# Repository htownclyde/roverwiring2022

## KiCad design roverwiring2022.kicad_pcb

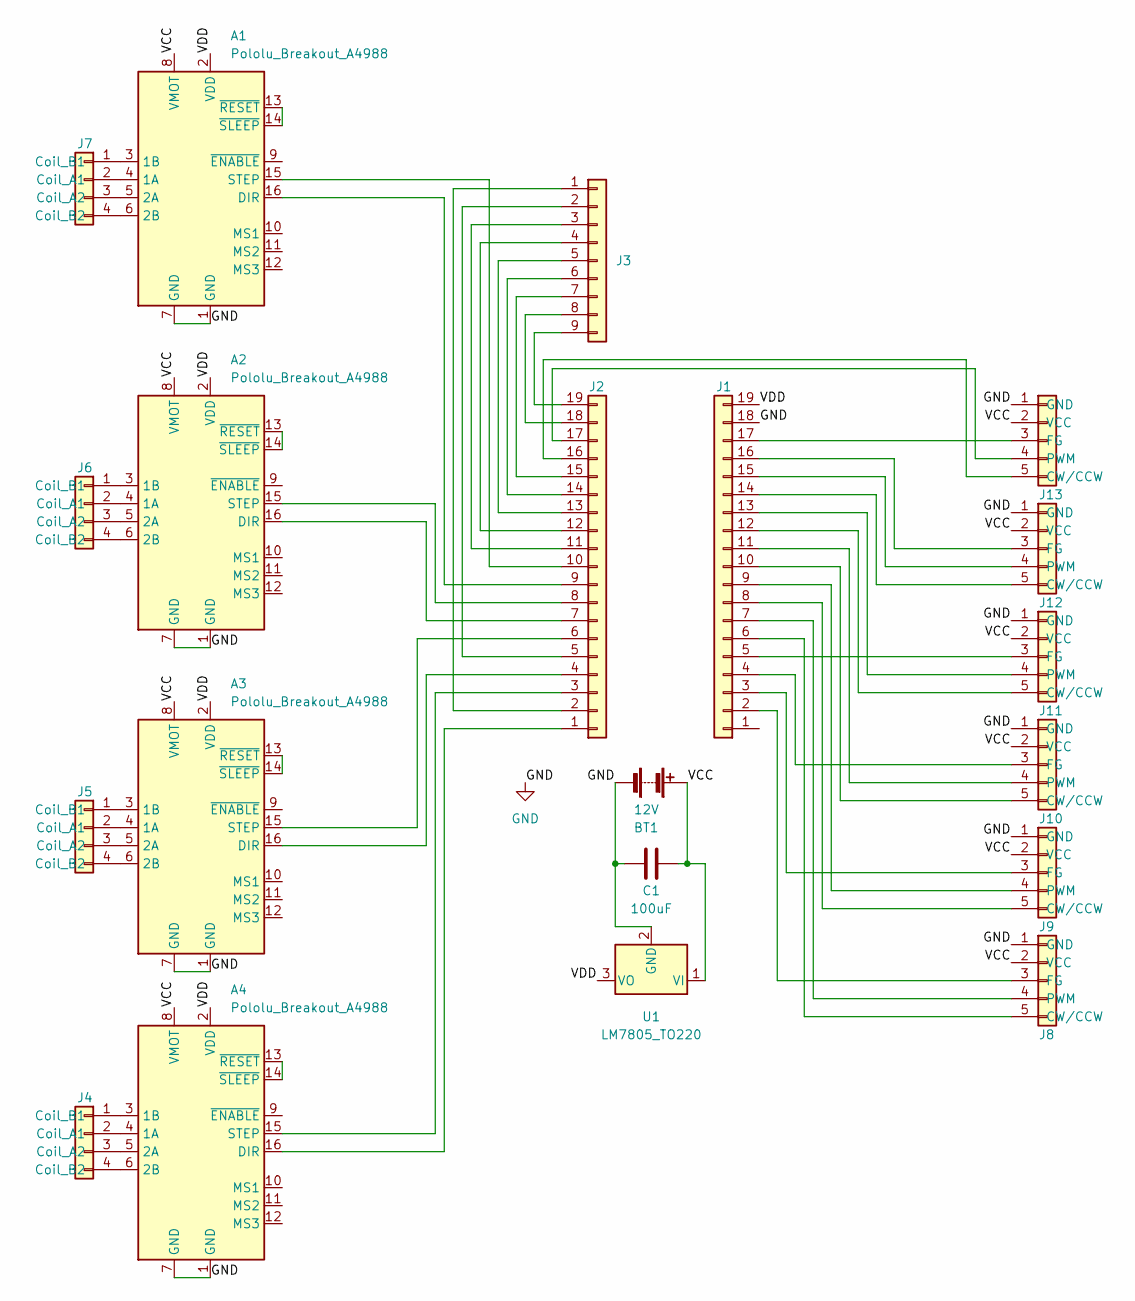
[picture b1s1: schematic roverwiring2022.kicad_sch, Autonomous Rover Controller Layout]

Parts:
A1, A2, A3, A4: Pololu_Breakout_A4988; Pololu_Breakout-16_15.2x20.3mm
BT1: 12V; BarrelJack_CLIFF_FC681465S_SMT_Horizontal
C1: 100uF; CP_Axial_L10.0mm_D4.5mm_P15.00mm_Horizontal
J1, J2: Conn_01x19; PinHeader_1x19_P2.54mm_Vertical
J3: Conn_01x09; PinHeader_1x09_P2.54mm_Vertical
J4, J5, J6, J7: Conn_01x04; PinHeader_1x04_P2.54mm_Vertical
J8, J9, J10, J11, J12, J13: Conn_01x05; PinHeader_1x05_P2.54mm_Vertical
U1: LM7805_TO220; TO-220-3_Vertical

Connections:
/VCC: A1.8 (VMOT), A2.8 (VMOT), A3.8 (VMOT), A4.8 (VMOT), BT1.1 (+), C1.2, J8.2 (VCC), J9.2 (VCC), J10.2 (VCC), J11.2 (VCC), J12.2 (VCC), J13.2 (VCC), U1.1 (VI)
/VDD: A1.2 (VDD), A2.2 (VDD), A3.2 (VDD), A4.2 (VDD), J1.19, U1.3 (VO)
GND: A1.1 (GND), A1.7 (GND), A2.1 (GND), A2.7 (GND), A3.1 (GND), A3.7 (GND), A4.1 (GND), A4.7 (GND), BT1.2 (-), C1.1, J1.18, J8.1 (GND), J9.1 (GND), J10.1 (GND), J11.1 (GND), J12.1 (GND), J13.1 (GND), U1.2 (GND)
unnamed: A1.3 (1B), J7.1 (Coil_B1)
unnamed: A1.4 (1A), J7.2 (Coil_A1)
unnamed: A1.5 (2A), J7.3 (Coil_A2)
unnamed: A1.6 (2B), J7.4 (Coil_B2)
unnamed: A1.13 (~RESET), A1.14 (~SLEEP)
unnamed: A1.15 (STEP), J2.10
unnamed: A1.16 (DIR), J2.9
unnamed: A2.3 (1B), J6.1 (Coil_B1)
unnamed: A2.4 (1A), J6.2 (Coil_A1)
unnamed: A2.5 (2A), J6.3 (Coil_A2)
unnamed: A2.6 (2B), J6.4 (Coil_B2)
unnamed: A2.13 (~RESET), A2.14 (~SLEEP)
unnamed: A2.15 (STEP), J2.8
unnamed: A2.16 (DIR), J2.7
unnamed: A3.3 (1B), J5.1 (Coil_B1)
unnamed: A3.4 (1A), J5.2 (Coil_A1)
unnamed: A3.5 (2A), J5.3 (Coil_A2)
unnamed: A3.6 (2B), J5.4 (Coil_B2)
unnamed: A3.13 (~RESET), A3.14 (~SLEEP)
unnamed: A3.15 (STEP), J2.6
unnamed: A3.16 (DIR), J2.4
unnamed: A4.3 (1B), J4.1 (Coil_B1)
unnamed: A4.4 (1A), J4.2 (Coil_A1)
unnamed: A4.5 (2A), J4.3 (Coil_A2)
unnamed: A4.6 (2B), J4.4 (Coil_B2)
unnamed: A4.13 (~RESET), A4.14 (~SLEEP)
unnamed: A4.15 (STEP), J2.3
unnamed: A4.16 (DIR), J2.1
unnamed: J1.2, J8.3 (FG)
unnamed: J1.3, J9.3 (FG)
unnamed: J1.4, J10.3 (FG)
unnamed: J1.5, J11.3 (FG)
unnamed: J1.6, J8.5 (CW/CCW)
unnamed: J1.7, J8.4 (PWM)
unnamed: J1.8, J9.5 (CW/CCW)
unnamed: J1.9, J9.4 (PWM)
unnamed: J1.10, J10.5 (CW/CCW)
unnamed: J1.11, J10.4 (PWM)
unnamed: J1.12, J11.5 (CW/CCW)
unnamed: J1.13, J11.4 (PWM)
unnamed: J1.14, J12.5 (CW/CCW)
unnamed: J1.15, J12.4 (PWM)
unnamed: J1.16, J12.3 (FG)
unnamed: J1.17, J13.3 (FG)
unnamed: J2.2, J3.1
unnamed: J2.5, J3.2
unnamed: J2.11, J3.3
unnamed: J2.12, J3.4
unnamed: J2.13, J3.5
unnamed: J2.14, J3.6
unnamed: J2.15, J3.7
unnamed: J2.18, J3.8
unnamed: J2.19, J3.9
unnamed: J2.17, J13.4 (PWM)
unnamed: J2.16, J13.5 (CW/CCW)

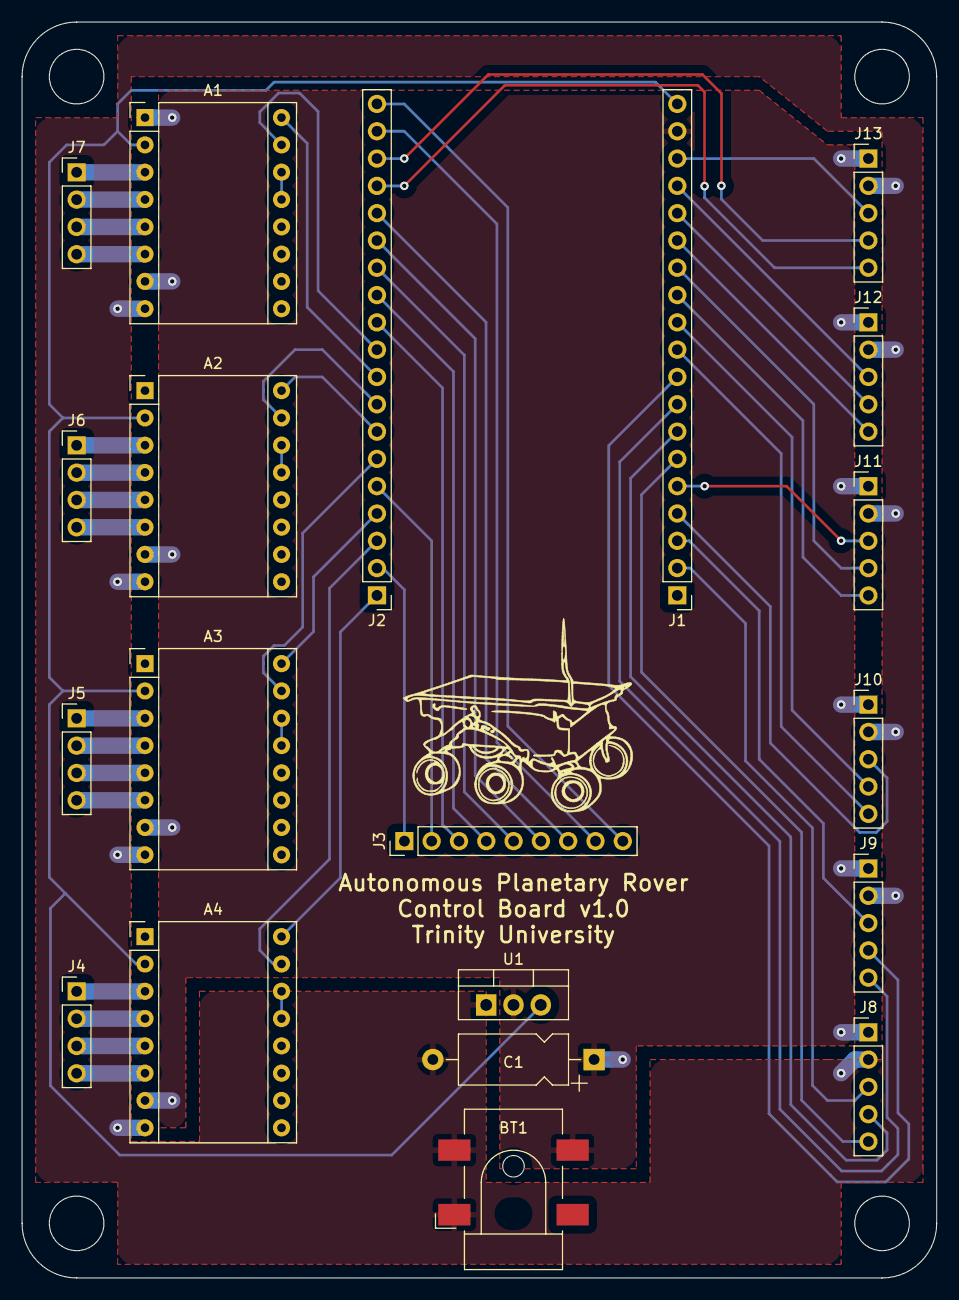
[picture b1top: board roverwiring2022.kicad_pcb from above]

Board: 2 copper layers, 85.1 x 116.8 mm, 20 parts (0 on the bottom side), 58 nets.

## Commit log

2022-11-06 first board revision
2022-11-06 removed
2022-11-07 updating traces to clear drc errors, widening power traces
2022-11-07 update gitignore
2022-11-07 resolved all outstanding drc conflicts and finished VCC and GND planes
2022-11-08 reshaped power planes, fixed gnd issue
2022-11-08 added backside ground plane
